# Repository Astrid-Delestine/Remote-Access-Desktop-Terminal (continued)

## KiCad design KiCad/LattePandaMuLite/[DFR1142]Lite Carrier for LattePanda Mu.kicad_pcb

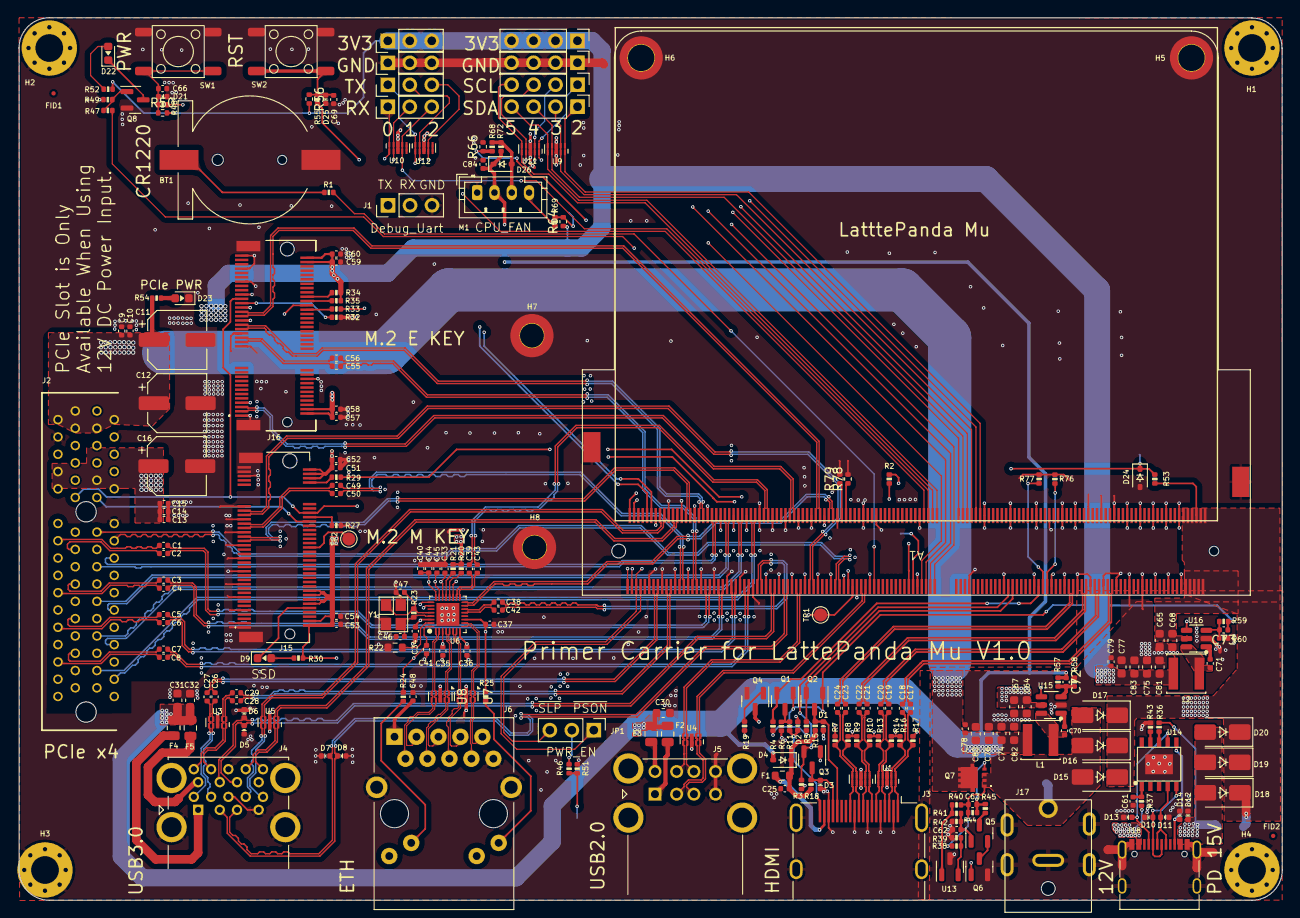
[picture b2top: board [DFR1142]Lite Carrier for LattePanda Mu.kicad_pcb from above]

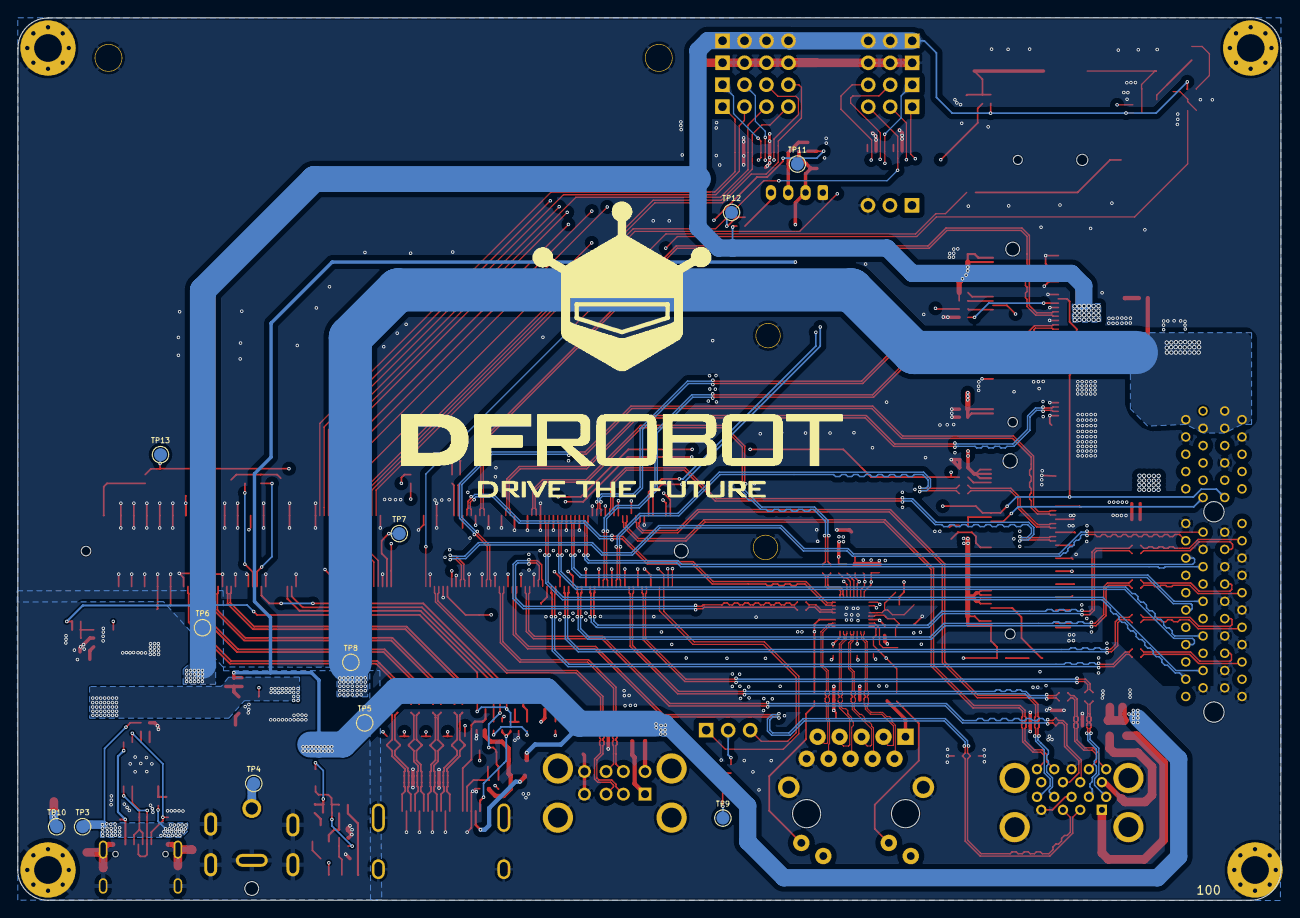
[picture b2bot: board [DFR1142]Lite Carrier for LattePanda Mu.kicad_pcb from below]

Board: 4 copper layers, 146.0 x 102.0 mm, 254 parts (11 on the bottom side), 204 nets.

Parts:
A1: LattePanda_Mu; LattePanda_Module_H8.0mm_Horizontal
BT1: Battery_Cell; Battery_Holder_CR1220_S8411-45R
C1, C2, C3, C4, C5, C6, C7, C8, C49, C50, C55, C56: 220nF/50V; C_0402_1005Metric
C9, C10, C13, C15, C17, C18, C19, C20, C21, C22, C23, C24, C25, C26, C27, C28, C29, C33, C34, C35, C36, C37, C38, C39, C40, C41, C42, C43, C45, C48, C52, C54, C58, C60, C70, C71, C78, C79, C84: 100nF/50V; C_0402_1005Metric
C11, C12: 100uF/25V; CP_Elec_6.3x7.7
C14, C44, C51, C53, C57, C59: 10uF/10V; C_0402_1005Metric
C16: 560uF/25V; CP_Elec_6.3x7.7
C30, C31, C32, C64, C65, C67, C68, C74, C75, C76, C77, C80, C81, C82, C83: 22uF/10V; C_0603_1608Metric
C46, C47, C72, C73: 12pF/50V; C_0402_1005Metric
C61, C62, C63, C66, C69: 1uF/16V; C_0402_1005Metric
D1, D2, D3, D5, D6, D7, D8, D10, D11, D21, D25: ESD5V0B03; D_0402_1005Metric
D4, D26: 1N5819WS; D_SOD-323
D9, D22, D23: LED_G; LED_0603_1608Metric
D12, D13, D14: PESD24VS1UL-N; D_0402_1005Metric
D15, D16, D17, D18, D19, D20: SS54; D_SMA
D24: 3V3 Izt=5mA; D_SOD-323
F1: 6V/50mA; R_0603_1608Metric
F2, F3: 6V/1A; Fuse_0805_2012Metric
F4: 6V/2A; R_0805_2012Metric
F5: 6V/2A; Fuse_0805_2012Metric
FID1, FID2: Fiducial; Fiducial_0.5mm_Mask1mm
H1, H2, H3, H4: MountingHole_Pad; MountingHole_3.2mm_M3_Pad_Via
H5, H6: MountingHole_Pad; MountingHole_3mm_M2_Pad_TopOnly
H7, H8: MountingHole_M2.0; MountingHole_2.7mm_M2_Pad_TopOnly
J1, J8, J10, J11, J14: Conn_01x03_Pin; PinHeader_1x03_P2.54mm_Vertical
J2: Bus_PCI_Express_x4; PCIe_x4_Gen3Slot_Connectors
J3: HDMI_A; HDMI_A_Molex_208658-1001_Horizontal
J4: USB3_A_Stacked; USB3_A_Molex_48406-0001_Horizontal_Stacked
J5: USB_A_Stacked; USB_A_CUI_UJ2-ADH-TH_Horizontal_Stacked
J6: RJ45_RB1-125B8G1A; RJ45_UDE_RB1-125B8G1A
J7, J9, J12, J13: Conn_01x04_Pin; PinHeader_1x04_P2.54mm_Vertical
J15: Bus_M.2_Socket_M; PCIe_M.2_Connectors_P=0.5mm_H=4.2mm_KeyM
J16: Bus_M.2_Socket_E; PCIe_M.2_Connectors_P=0.5mm_H=4.2mm_KeyE
J17: Barrel_Jack_Switch; DC_Jack_DC007B_30V_10A
J18: USB_C_Receptacle_USB2.0; USB_C_Receptacle_G-Switch_GT-USB-7010ASV
JP1: Jumper_3_Bridged12; PinHeader_1x03_P2.54mm_Vertical
L1, L2: 2.2uH/4.3A; L_Sunlord_SWPA4020S
M1: Fan_4pin; JST_PH_B4B-PH-K_1x04_P2.00mm_Vertical
Q1, Q5, Q6, Q8: 2N7002; SOT-23
Q2, Q3, Q4: 2SK3018; SOT-23
Q7: NCE30P28Q; MOSFET_PDFN8_3.3x3.3
R1, R11, R37, R47: 1K/1%; R_0402_1005Metric
R2, R20, R21, R34, R35, R36, R38, R40, R49, R50, R56, R58, R78, R79: 10K/1%; R_0402_1005Metric
R3, R5, R15, R18, R19, R30, R39, R52, R53: 2.2K/1%; R_0402_1005Metric
R4, R23: 1M/1%; R_0402_1005Metric
R6, R41, R42, R54, R59, R66, R68: 21.5K/1%; R_0402_1005Metric
R7, R8, R9, R10, R13, R14, R16, R17, R24, R25: 470R/1%; R_0402_1005Metric
R22: 2.49K/1%; R_0603_1608Metric
R27, R29, R32, R33: 0R/1%; R_0402_1005Metric
R43: 56K/1%; R_0402_1005Metric
R44, R45, R51, R76, R77: 100K/1%; R_0402_1005Metric
R46, R48, R55, R69: 100R/1%; R_0402_1005Metric
R57: 75K/1%; R_0402_1005Metric
R60, R64, R72: 4.7K/1%; R_0402_1005Metric
SW1, SW2: SW_Push; SW_Push_6x6x6
TP1, TP2, TP3, TP4, TP5, TP6, TP7, TP8, TP9, TP10, TP11, TP12, TP13: TestPoint; TestPoint_Pad_D1.5mm
U1, U2: TPAZ1023-04F; Diodes_UDFN-10_1.0x2.5mm_P0.5mm
U3, U4, U5, U7, U8, U9, U10, U11, U12: ULC0524P; Diodes_UDFN-10_1.0x2.5mm_P0.5mm
U6: RTL8111H-CG-RH; QFN-32-1EP_4x4mm_P0.4mm_EP2.65x2.65mm
U13: TL431DBZ; SOT-23
U14: CH224K; ESSOP-10-1EP_3.9x5mm_P1.0mm_EP3.2x2.3
U15, U16: SY8253ADC; TSOT-23-6
Y1: 25MHz; Crystal_SMD_3225-4Pin_3.2x2.5mm

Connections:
5V_HDMI_VCC: C25.1, D4.1 (K), F1.1, R15.1, R18.1
+1V0: C33.2, C34.2, C35.2, C36.2, C40.2, C44.2, U6.3 (AVDD10), U6.8 (AVDD10), U6.22 (DVDD10), U6.24 (REGOUT), U6.30 (AVDD10)
+3V3: C13.2, C14.2, C15.1, C16.1, C37.2, C41.2, C45.2, C51.2, C52.2, C53.2, C54.2, C57.2, C58.2, C59.2, C60.2, C73.1, C75.2, C77.2, C79.1, C81.2, C83.2, J2.A9 (+3.3V), J2.A10 (+3.3V), J2.B8 (+3.3V), J2.B10 (3.3Vaux), J13.1, J13.2, J13.3, J13.4, J14.1, J14.2, J14.3, J15.2 (3.3V), J15.4 (3.3V), J15.12 (3.3V), J15.14 (3.3V), J15.16 (3.3V), J15.18 (3.3V), J15.70 (3.3V), J15.72 (3.3V), J15.74 (3.3V), J16.2 (3.3V), J16.4 (3.3V), J16.72 (3.3V), J16.74 (3.3V), L2.2, Q1.1 (G), Q2.1 (G), Q3.1 (G), R3.1, R4.1, R5.1, R20.1, R21.1, R24.2, R25.2, R30.2, R34.2, R35.1, R50.2, R52.2, R56.2, R59.2, R64.1, TP6.1, U6.11 (AVDD33), U6.23 (VDDREG), U6.32 (AVDD33)
+5V: C30.2, C31.2, C32.2, C72.1, C74.2, C76.2, C78.1, C80.2, C82.2, C84.1, D4.2 (A), D26.1 (K), F2.1, F3.1, F4.1, F5.1, L1.2, M1.2 (+), R57.2, R72.1, TP5.1
+12V: C63.2, D15.2 (A), D16.2 (A), D17.2 (A), J17.1, Q7.1 (S_1), Q7.2 (S_2), Q7.3 (S_3), R38.2, R40.2, R44.2, TP4.1
+12VA: C9.1, C10.1, C11.1, C12.1, J2.A2 (+12V), J2.A3 (+12V), J2.B1 (+12V), J2.B2 (+12V), J2.B3 (+12V), Q7.5 (D_1), Q7.6 (D_2), Q7.7 (D_3), Q7.8 (D_4), Q7.9 (D_5), Q7.10 (D_6), Q7.11 (D_7), R54.1, TP8.1
+15V: D12.1 (K), D18.2 (A), D19.2 (A), D20.2 (A), J18.A4 (VBUS), J18.A9 (VBUS), J18.B4 (VBUS), J18.B9 (VBUS), R36.1, R37.1, TP3.1
+BATT: A1.115 (VBAT), R1.1
/Fan_Temp/FAN_1_PWM: A1.2 (FAN1_PWM), R64.2, R69.1, TP12.1
/Fan_Temp/FAN_1_TAC: A1.4 (FAN1_TAC), R66.1, R68.2, TP11.1
/GPIO/I2C2_SCL: A1.154 (I2C2_SCL), J9.1, U11.1, U11.10 (NC)
/GPIO/I2C2_SDA: A1.156 (I2C2_SDA), J7.1, U9.1, U9.10 (NC)
/GPIO/I2C3_SCL: A1.150 (I2C3_SCL), J9.2, U11.2, U11.9 (NC)
/GPIO/I2C3_SDA: A1.152 (I2C3_SDA), J7.2, U9.2, U9.9 (NC)
/GPIO/I2C4_SCL: A1.146 (I2C4_SCL), J9.3, U11.4, U11.7 (NC)
/GPIO/I2C4_SDA: A1.148 (I2C4_SDA), J7.3, U9.4, U9.7 (NC)
/GPIO/I2C5_SCL: A1.142 (I2C5_SCL), J9.4, U11.5, U11.6 (NC)
/GPIO/I2C5_SDA: A1.144 (I2C5_SDA), J7.4, U9.5, U9.6 (NC)
/GPIO/SOC_UART0_RX: A1.137 (UART0_RXD), J8.1, U10.1, U10.10 (NC)
/GPIO/SOC_UART0_TX: A1.139 (UART0_TXD), J10.1, U12.1, U12.10 (NC)
/GPIO/SOC_UART1_RX: A1.141 (UART1_RXD), J8.2, U10.2, U10.9 (NC)
/GPIO/SOC_UART1_TX: A1.143 (UART1_TXD), J10.2, U12.2, U12.9 (NC)
/GPIO/SOC_UART2_RX: A1.140 (UART2_RXD), J8.3, U10.4, U10.7 (NC)
/GPIO/SOC_UART2_TX: A1.138 (UART2_TXD), J10.3, U12.4, U12.7 (NC)
/Gigabit Ethernet/GbE_PCIe_CLK+: A1.94 (REFCLK4+), U6.15 (REFCLK_P)
/Gigabit Ethernet/GbE_PCIe_CLK-: A1.96 (REFCLK4-), U6.16 (REFCLK_N)
/Gigabit Ethernet/GbE_PCIe_RX+: A1.64 (HSIO6_RX+), C43.2
/Gigabit Ethernet/GbE_PCIe_RX-: A1.66 (HSIO6_RX-), C39.2
/Gigabit Ethernet/GbE_PCIe_TX+: A1.61 (HSIO6_TX+), C42.2
/Gigabit Ethernet/GbE_PCIe_TX-: A1.63 (HSIO6_TX-), C38.2
/Gigabit Ethernet/HSI+: C42.1, U6.13 (HSIP)
/Gigabit Ethernet/HSI-: C38.1, U6.14 (HSIN)
/Gigabit Ethernet/HSO+: C43.1, U6.17 (HSOP)
/Gigabit Ethernet/HSO-: C39.1, U6.18 (HSON)
/Gigabit Ethernet/LED1_1000: J6.L4, U6.26 (LED1)
/Gigabit Ethernet/LED2_ACT: J6.L2, U6.25 (LED2)
/Gigabit Ethernet/MDI0+: J6.R2 (TD1+), U6.1 (MDIP0), U8.5, U8.6 (NC)
/Gigabit Ethernet/MDI0-: J6.R3 (TD1-), U6.2 (MDIN0), U8.4, U8.7 (NC)
/Gigabit Ethernet/MDI1+: J6.R4 (TD2+), U6.4 (MDIP1), U8.2, U8.9 (NC)
/Gigabit Ethernet/MDI1-: J6.R5 (TD2-), U6.5 (MDIN1), U8.1, U8.10 (NC)
/Gigabit Ethernet/MDI2+: J6.R6 (TD3+), U6.6 (MDIP2), U7.5, U7.6 (NC)
/Gigabit Ethernet/MDI2-: J6.R7 (TD3-), U6.7 (MDIN2), U7.4, U7.7 (NC)
/Gigabit Ethernet/MDI3+: J6.R8 (TD4+), U6.9 (MDIP3), U7.2, U7.9 (NC)
/Gigabit Ethernet/MDI3-: J6.R9 (TD4-), U6.10 (MDIN3), U7.1, U7.10 (NC)
/HDMI/DDC_SCL: D1.2 (A2), J3.15 (SCL), Q2.3 (D), R15.2
/HDMI/DDC_SDA: D3.2 (A2), J3.16 (SDA), Q3.3 (D), R18.2
/HDMI/DDI_B_DDC_SCL: A1.171 (DDIB_DDC_SCL), Q2.2 (S), R5.2
/HDMI/DDI_B_DDC_SDA: A1.169 (DDIB_DDC_SDA), Q3.2 (S), R3.2
/HDMI/DDI_B_HPD: A1.183 (DDIB_HPD), Q1.2 (S), R4.2
/HDMI/DDI_B_TX0+: A1.217 (DDIB_TX0+), C17.1
/HDMI/DDI_B_TX0-: A1.215 (DDIB_TX0-), C18.1
/HDMI/DDI_B_TX1+: A1.211 (DDIB_TX1+), C19.1
/HDMI/DDI_B_TX1-: A1.209 (DDIB_TX1-), C20.1
/HDMI/DDI_B_TX2+: A1.205 (DDIB_TX2+), C21.1
/HDMI/DDI_B_TX2-: A1.203 (DDIB_TX2-), C22.1
/HDMI/DDI_B_TX3+: A1.199 (DDIB_TX3+), C23.1
/HDMI/DDI_B_TX3-: A1.197 (DDIB_TX3-), C24.1
/HDMI/HPD: D2.2 (A2), J3.19 (HPD), R11.2
/HDMI/TMDS_CK+: C23.2, J3.10 (CK+), R8.1, U2.4, U2.7 (NC)
/HDMI/TMDS_CK-: C24.2, J3.12 (CK-), R7.1, U2.5, U2.6 (NC)
/HDMI/TMDS_D0+: C21.2, J3.7 (D0+), R10.1, U2.1, U2.10 (NC)
/HDMI/TMDS_D0-: C22.2, J3.9 (D0-), R9.1, U2.2, U2.9 (NC)
/HDMI/TMDS_D1+: C19.2, J3.4 (D1+), R14.1, U1.4, U1.7 (NC)
/HDMI/TMDS_D1-: C20.2, J3.6 (D1-), R13.1, U1.5, U1.6 (NC)
/HDMI/TMDS_D2+: C17.2, J3.1 (D2+), R17.1, U1.1, U1.10 (NC)
/HDMI/TMDS_D2-: C18.2, J3.3 (D2-), R16.1, U1.2, U1.9 (NC)
/LattePanda Module/HSIO_0_TX+: A1.13 (HSIO0_TX+), C27.1
/LattePanda Module/HSIO_0_TX-: A1.15 (HSIO0_TX-), C26.1
/LattePanda Module/HSIO_1_TX+: A1.19 (HSIO1_TX+), C29.1
/LattePanda Module/HSIO_1_TX-: A1.21 (HSIO1_TX-), C28.1
/LattePanda Module/HSIO_2_RX+: A1.28 (HSIO2_RX+), J15.43 (PERp0/SATA-B-)
/LattePanda Module/HSIO_2_RX-: A1.30 (HSIO2_RX-), J15.41 (PERn0/SATA-B+)
/LattePanda Module/HSIO_2_TX+: A1.25 (HSIO2_TX+), C49.1
/LattePanda Module/HSIO_2_TX-: A1.27 (HSIO2_TX-), C50.1
/LattePanda Module/HSIO_3_RX+: A1.34 (HSIO3_RX+), J16.41 (PERp0)
/LattePanda Module/HSIO_3_RX-: A1.36 (HSIO3_RX-), J16.43 (PERn0)
/LattePanda Module/HSIO_3_TX+: A1.31 (HSIO3_TX+), C55.1
/LattePanda Module/HSIO_3_TX-: A1.33 (HSIO3_TX-), C56.1
/LattePanda Module/HSIO_8_RX+: A1.40 (HSIO8_RX+), J2.A16 (PERp0)
/LattePanda Module/HSIO_8_RX-: A1.42 (HSIO8_RX-), J2.A17 (PERn0)
/LattePanda Module/HSIO_8_TX+: A1.37 (HSIO8_TX+), C1.1
/LattePanda Module/HSIO_8_TX-: A1.39 (HSIO8_TX-), C2.1
/LattePanda Module/HSIO_9_RX+: A1.46 (HSIO9_RX+), J2.A21 (PERp1)
/LattePanda Module/HSIO_9_RX-: A1.48 (HSIO9_RX-), J2.A22 (PERn1)
/LattePanda Module/HSIO_9_TX+: A1.43 (HSIO9_TX+), C3.1
/LattePanda Module/HSIO_9_TX-: A1.45 (HSIO9_TX-), C4.1
/LattePanda Module/HSIO_10_RX+: A1.52 (HSIO10_RX+), J2.A25 (PERp2)
/LattePanda Module/HSIO_10_RX-: A1.54 (HSIO10_RX-), J2.A26 (PERn2)
/LattePanda Module/HSIO_10_TX+: A1.49 (HSIO10_TX+), C5.1
/LattePanda Module/HSIO_10_TX-: A1.51 (HSIO10_TX-), C6.1
/LattePanda Module/HSIO_11_RX+: A1.58 (HSIO11_RX+), J2.A29 (PERp3)
/LattePanda Module/HSIO_11_RX-: A1.60 (HSIO11_RX-), J2.A30 (PERn3)
/LattePanda Module/HSIO_11_TX+: A1.55 (HSIO11_TX+), C7.1
/LattePanda Module/HSIO_11_TX-: A1.57 (HSIO11_TX-), C8.1
/LattePanda Module/REFCLK0+: A1.85 (REFCLK0+), J15.53 (REFCLKn)
/LattePanda Module/REFCLK0-: A1.87 (REFCLK0-), J15.55 (REFCLKp)
/LattePanda Module/REFCLK2+: A1.97 (REFCLK2+), J2.A13 (REFCLK+)
/LattePanda Module/REFCLK2-: A1.99 (REFCLK2-), J2.A14 (REFCLK-)
/LattePanda Module/REFCLK3+: A1.88 (REFCLK3+), J16.47 (REFCLKp0)
/LattePanda Module/REFCLK3-: A1.90 (REFCLK3-), J16.49 (REFCLKn0)
/LattePanda Module/SLS_S3: A1.7 (SLS_S3), JP1.3 (B)
/LattePanda Module/SUSCLK_WIFI: A1.131 (SUSCLK), R29.2, R33.2
/LattePanda Module/USB_2_P7+: A1.76 (USB2_P7+), J16.3 (USB_D+)
/LattePanda Module/USB_2_P7-: A1.78 (USB2_P7-), J16.5 (USB_D-)
/LattePanda Module/~PWR_SW: A1.1 (~PWRBTN), R48.2
/LattePanda Module/~RST_SW: A1.3 (~RSTBTN), R55.2
/M.2 E&M Key/CON_PCIE_TX_0+: C55.2, J16.35 (PETp0)
/M.2 E&M Key/CON_PCIE_TX_0-: C56.2, J16.37 (PETn0)
/M.2 E&M Key/CON_PCIE_TX_1+: C49.2, J15.49 (PETp0/SATA-A+)
/M.2 E&M Key/CON_PCIE_TX_1-: C50.2, J15.47 (PETn0/SATA-A-)
/M.2 E&M Key/~CLKREQE: J16.53 (~CLKREQ3), R32.1
/M.2 E&M Key/~CLKREQM: J15.52 (~CLKREQ), R27.1
/PCIe x4/PCIE30_TX0_N: C2.2, J2.B15 (PETn0)
/PCIe x4/PCIE30_TX0_P: C1.2, J2.B14 (PETp0)
/PCIe x4/PCIE30_TX1_N: C4.2, J2.B20 (PETn1)
/PCIe x4/PCIE30_TX1_P: C3.2, J2.B19 (PETp1)
/PCIe x4/PCIE30_TX2_N: C6.2, J2.B24 (PETn2)
/PCIe x4/PCIE30_TX2_P: C5.2, J2.B23 (PETp2)
/PCIe x4/PCIE30_TX3_N: C8.2, J2.B28 (PETn3)
/PCIe x4/PCIE30_TX3_P: C7.2, J2.B27 (PETp3)
/PSU/CC1: D13.1 (K), J18.A5 (CC1), U14.7 (CC1)
/PSU/CC2: D14.1 (K), J18.B5 (CC2), U14.6 (CC2)
/PSU/PWR_C_D+: D11.2 (A2), J18.A6 (D+), J18.B6 (D+), U14.4 (DP)
/PSU/PWR_C_D-: D10.2 (A2), J18.A7 (D-), J18.B7 (D-), U14.5 (DM)
/PSU/PWR_EN: Q6.1 (G), R46.2, R51.2, TP9.1, U15.4 (EN), U16.4 (EN)
/USB2.0&USB3.0/CON_USB1_D_N: A1.109 (USB2_P5-), J5.2 (D1-), U4.2, U4.9 (NC)
/USB2.0&USB3.0/CON_USB1_D_P: A1.111 (USB2_P5+), J5.3 (D1+), U4.1, U4.10 (NC)
/USB2.0&USB3.0/CON_USB2_D_N: A1.79 (USB2_P3-), J5.6 (D2-), U4.5, U4.6 (NC)
/USB2.0&USB3.0/CON_USB2_D_P: A1.81 (USB2_P3+), J5.7 (D2+), U4.4, U4.7 (NC)
/USB2.0&USB3.0/CON_USB3_D_N: A1.73 (USB2_P2-), D8.2 (A2), J4.2 (D1-)
/USB2.0&USB3.0/CON_USB3_D_P: A1.75 (USB2_P2+), D7.2 (A2), J4.3 (D1+)
/USB2.0&USB3.0/CON_USB3_SSRX_N: A1.18 (HSIO0_RX-), J4.5 (SSRX1-), U5.4, U5.7 (NC)
/USB2.0&USB3.0/CON_USB3_SSRX_P: A1.16 (HSIO0_RX+), J4.6 (SSRX1+), U5.5, U5.6 (NC)
/USB2.0&USB3.0/CON_USB3_SSTX_N: C26.2, J4.8 (SSTX1-), U3.4, U3.7 (NC)
/USB2.0&USB3.0/CON_USB3_SSTX_P: C27.2, J4.9 (SSTX1+), U3.5, U3.6 (NC)
/USB2.0&USB3.0/CON_USB4_D_N: A1.67 (USB2_P1-), D6.2 (A2), J4.11 (D2-)
/USB2.0&USB3.0/CON_USB4_D_P: A1.69 (USB2_P1+), D5.2 (A2), J4.12 (D2+)
/USB2.0&USB3.0/CON_USB4_SSRX_N: A1.24 (HSIO1_RX-), J4.14 (SSRX2-), U5.1, U5.10 (NC)
/USB2.0&USB3.0/CON_USB4_SSRX_P: A1.22 (HSIO1_RX+), J4.15 (SSRX2+), U5.2, U5.9 (NC)
/USB2.0&USB3.0/CON_USB4_SSTX_N: C28.2, J4.17 (SSTX2-), U3.1, U3.10 (NC)
/USB2.0&USB3.0/CON_USB4_SSTX_P: C29.2, J4.18 (SSTX2+), U3.2, U3.9 (NC)
/~PLT_RST: A1.105 (~PLTRST), J2.A11 (~PERST), J15.50 (~PERST), J16.52 (~PERST0), TP1.1, U6.19 (PERSTB)
/~PWR_LED/~PSON: A1.5 (SLS_S0), JP1.1 (A), R19.1, R47.1
/~WAKE: A1.103 (~WAKE), J2.B11 (~WAKE), J15.54 (~PEWAKE), J16.55 (~PEWAKE0)
GND: A1.11 (GND), A1.14 (GND), A1.17 (GND), A1.20 (GND), A1.23 (GND), A1.26 (GND), A1.29 (GND), A1.32 (GND), A1.35 (GND), A1.38 (GND), A1.41 (GND), A1.44 (GND), A1.47 (GND), A1.50 (GND), A1.53 (GND), A1.56 (GND), A1.59 (GND), A1.62 (GND), A1.65 (GND), A1.68 (GND), A1.71 (GND), A1.74 (GND), A1.77 (GND), A1.80 (GND), A1.83 (GND), A1.86 (GND), A1.89 (GND), A1.92 (GND), A1.95 (GND), A1.98 (GND), A1.101 (GND), A1.107 (GND), A1.110 (GND), A1.113 (GND), A1.116 (GND), A1.135 (GND), A1.136 (GND), A1.151 (GND), A1.158 (GND), A1.167 (GND), A1.170 (GND), A1.181 (GND), A1.182 (GND), A1.188 (GND), A1.189 (GND), A1.194 (GND), A1.195 (GND), A1.200 (GND), A1.201 (GND), A1.206 (GND), A1.207 (GND), A1.212 (GND), A1.213 (GND), A1.218 (GND), A1.219 (GND), A1.224 (GND), A1.225 (GND), A1.230 (GND), A1.231 (GND), A1.236 (GND), A1.237 (GND), A1.242 (GND), A1.243 (GND), A1.248 (GND), A1.249 (GND), A1.MP (Mountinge_Pads), BT1.2 (-), C9.2, C10.2, C11.2, C12.2, C13.1, C14.1, C15.2, C16.2, C25.2, C30.1, C31.1, C32.1, C33.1, C34.1, C35.1, C36.1, C37.1, C40.1, C41.1, C44.1, C45.1, C46.1, C47.1, C48.2, C51.1, C52.1, C53.1, C54.1, C57.1, C58.1, C59.1, C60.1, C61.2, C62.2, C64.1, C65.1, C66.2, C67.1, C68.1, C69.2, C74.1, C75.1, C76.1, C77.1, C78.2, C79.2, C80.1, C81.1, C82.1, C83.1, C84.2, D1.1 (A1), D2.1 (A1), D3.1 (A1), D5.1 (A1), D6.1 (A1), D7.1 (A1), D8.1 (A1), D10.1 (A1), D11.1 (A1), D12.2 (A), D13.2 (A), D14.2 (A), D21.1 (A1), D23.1 (K), D24.2 (A), D25.1 (A1), H1.1, H2.1, H3.1, H4.1, H5.1, H6.1, H7.1, H8.1, J1.3, J2.A1 (~PRSNT1), J2.A4 (GND), J2.A12 (GND), J2.A15 (GND), J2.A18 (GND), J2.A20 (GND), J2.A23 (GND), J2.A24 (GND), J2.A27 (GND), J2.A28 (GND), J2.A31 (GND), J2.B4 (GND), J2.B7 (GND), J2.B13 (GND), J2.B16 (GND), J2.B17 (~PRSNT2), J2.B18 (GND), J2.B21 (GND), J2.B22 (GND), J2.B25 (GND), J2.B26 (GND), J2.B29 (GND), J2.B31 (~PRSNT2), J2.B32 (GND), J3.2 (D2S), J3.5 (D1S), J3.8 (D0S), J3.11 (CKS), J3.17 (GND), J3.SH, J4.4 (GND1), J4.7 (DRAIN1), J4.13 (GND2), J4.16 (DRAIN2), J4.19 (SHIELD), J5.4 (GND1), J5.8 (GND2), J5.9 (Shield), J6.R10 (GND), J6.SH, J11.1, J11.2, J11.3, J12.1, J12.2, J12.3, J12.4, J15.1 (GND), J15.3 (GND), J15.9 (GND), J15.15 (GND), J15.21 (GND), J15.27 (GND), J15.33 (GND), J15.39 (GND), J15.45 (GND), J15.51 (GND), J15.57 (GND), J15.71 (GND), J15.73 (GND), J15.75 (GND), J15.MP1, J15.MP2, J16.1 (GND), J16.7 (GND), J16.18 (GND), J16.33 (GND), J16.39 (GND), J16.45 (GND), J16.51 (GND), J16.57 (GND), J16.63 (GND), J16.69 (GND), J16.75 (GND), J16.MP1, J16.MP2, J17.2, J17.3, J18.A1 (GND), J18.A12 (GND), J18.B1 (GND), J18.B12 (GND), J18.S1 (SHIELD), M1.1 (-), Q4.2 (S), Q6.2 (S), Q8.2 (S), R6.2, R22.1, R27.2, R32.2, R39.1, R42.1, R43.2, R49.1, R51.1, R58.1, R60.1, R66.2, R76.2, R77.2, R78.2, R79.2, SW1.2, SW2.2, U1.3 (VSS), U1.8 (VSS), U2.3 (VSS), U2.8 (VSS), U3.3 (VSS), U3.8 (VSS), U4.3 (VSS), U4.8 (VSS), U5.3 (VSS), U5.8 (VSS), U6.33 (GND), U7.3 (VSS), U7.8 (VSS), U8.3 (VSS), U8.8 (VSS), U9.3 (VSS), U9.8 (VSS), U10.3 (VSS), U10.8 (VSS), U11.3 (VSS), U11.8 (VSS), U12.3 (VSS), U12.8 (VSS), U13.3 (A), U14.0 (GND), U15.2 (GND), U16.2 (GND), Y1.2, Y1.4
unnamed: A1.12 (SIO_UART_RX), J1.2
unnamed: A1.10 (SIO_UART_TX), J1.1
unnamed: A1.187 (TCP0_HPD), R76.1
unnamed: A1.185 (TCP1_HPD), R77.1
unnamed: A1.133 (~BIOS_SEL), R2.1, TP7.1
unnamed: A1.100 (~CLKREQ3), R79.1
unnamed: A1.102 (~CLKREQ4), R78.1
unnamed: BT1.1 (+), R1.2
unnamed: D9.2 (A), R30.1
unnamed: D9.1 (K), J15.10 (DAS/~DSS/~LED1)
unnamed: C66.1, D21.2 (A2), R48.1, R50.1, SW1.1
unnamed: D22.2 (A), R52.1
unnamed: D22.1 (K), Q8.3 (D)
unnamed: D23.2 (A), R54.2
unnamed: C69.1, D25.2 (A2), R55.1, R56.1, SW2.1
unnamed: D26.2 (A), M1.3 (Tacho), R68.1, R72.2
unnamed: F1.2, J3.18 (+5V)
unnamed: F4.2, J4.1 (VBUS1)
unnamed: F5.2, J4.10 (VBUS2)
unnamed: F2.2, J5.1 (VBUS1)
unnamed: F3.2, J5.5 (VBUS2)
unnamed: C48.1, J6.R1 (CT)
unnamed: J6.L1, R25.1
unnamed: J6.L3, R24.1
unnamed: J15.38 (DEVSLP), TP2.1
unnamed: J15.68 (SUSCLK), R29.1
unnamed: J16.50 (SUSCLK), R33.1
unnamed: J16.56 (~W_DISABLE1), R34.1
unnamed: J16.54 (~W_DISABLE2), R35.2
unnamed: JP1.2 (C), R46.1
unnamed: M1.4 (PWM), R69.2
unnamed: Q1.3 (D), R6.1, R11.1
unnamed: Q4.3 (D), R7.2, R8.2, R9.2, R10.2, R13.2, R14.2, R16.2, R17.2
unnamed: Q4.1 (G), R19.2
unnamed: Q5.3 (D), R45.1
unnamed: C62.1, Q5.1 (G), R41.1, R42.2
unnamed: Q5.2 (S), Q6.3 (D)
unnamed: C63.1, Q7.4 (G), R44.1, R45.2
unnamed: Q8.1 (G), R47.2, R49.2
unnamed: C47.2, R23.2, U6.28 (CKXTAL1), Y1.1
unnamed: C46.2, R23.1, U6.29 (CKXTAL2), Y1.3
unnamed: R20.2, U6.20 (ISOLATEB)
unnamed: R21.2, U6.21 (LANWAKEB)
unnamed: R22.2, U6.31 (RSET)
unnamed: U10.5, U10.6 (NC)
unnamed: U12.5, U12.6 (NC)
unnamed: R40.1, R41.2, U13.1 (K)
unnamed: R38.1, R39.2, U13.2 (REF)
unnamed: R43.1, U14.9 (CFG1)
unnamed: R36.2, U14.8 (VBUS)
unnamed: C61.1, R37.2, U14.1 (VDD)
unnamed: C70.2, U15.1 (BOOST)
unnamed: C72.2, R57.1, R58.2, U15.3 (FB)
unnamed: C70.1, L1.1, U15.6 (SW)
unnamed: C71.2, U16.1 (BOOST)
unnamed: C73.2, R59.1, R60.2, U16.3 (FB)
unnamed: C71.1, L2.1, U16.6 (SW)
VDC: A1.250 (VIN), A1.251 (VIN), A1.252 (VIN), A1.253 (VIN), A1.254 (VIN), A1.255 (VIN), A1.256 (VIN), A1.257 (VIN), A1.258 (VIN), A1.259 (VIN), A1.260 (VIN), C64.2, C65.2, C67.2, C68.2, D15.1 (K), D16.1 (K), D17.1 (K), D18.1 (K), D19.1 (K), D20.1 (K), R53.1, TP10.1, U15.5 (VIN), U16.5 (VIN)
VPullup: D24.1 (K), R2.2, R53.2, TP13.1

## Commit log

2024-12-18 Create Kicad Files
2025-01-10 setup for more in depth work
2025-01-10 Added Notes
2025-01-12 Add logs and update keyboard
2025-01-12 Update gitignore to not include invoices
2025-01-17 Update note2.md
    added more keyboard options to try
2025-01-21 Weekend work updates
2025-01-22 Create anntenna.md
    Added antenna areas of doc
2025-02-04 Create note3.md
    added note 3 regarding BMS stuff
2025-02-05 Add data from KiCAD and review
2025-02-07 kiCad BMS sadness
2025-02-08 finalized midterm review
2025-02-08 added list of goals for next 5 wks
2025-02-08 modified the table on bms info
2025-02-10 BMS circuitry
2025-02-12 Added kicad USBC controller and connected VBUS
2025-02-12 tb4 prooved to be too diffucult/expensive...
    Issue: would cost $200+ to devlop for this chipset
2025-02-12 added file note4.md
2025-02-13 updated time log
2025-02-17 Update BMS
2025-02-17 Added new files
2025-02-20 Add new notes; update component references in schematics and footprints, and complete charging design
2025-02-24 VRM update?
2025-02-24 remove VRM b.c naming broke
2025-02-24 add back VRM
2025-02-24 added volage stuffs
2025-02-25 Update VRM stuff
2025-02-26 Added example and updated power path
2025-02-26 Modified Power Stages
2025-02-26 Connected m.2 E Key
2025-02-27 Added HDMI connection and marked section for review in schematics; updated column widths in PRL file; added new operating values CSV files for power calculations.
2025-02-27 Started process of BMS review
2025-02-28 2x checked all schematics
2025-02-28 Pre-Annotate FULL, add usb
2025-03-02 Added Libs and DOCS
2025-03-02 Added Generated BOM
2025-03-02 Update BOM
2025-03-03 Sourced and documented all parts
2025-03-03 Push before Board Layout
2025-03-03 placed board components, with errors
2025-03-03 Removed Old BOM data
2025-03-03 Update Merged_BOM_Data
    part #s added
2025-03-03 Updated Layout
2025-03-04 Placed a lot of components
2025-03-05 added Trace width table
2025-03-06 End Of day commit
2025-03-06 Most of the way thru routing
2025-03-07 Wrong footprint for keyswitches, creating save point
2025-03-07 push prior to autorouting
2025-03-08 Adequitely Passing DRC
2025-03-08 finalized board layout
2025-03-10 2x checing of bom on JLCPCB
2025-03-11 Generate Gerbers and Order PCB
2025-06-27 Added the License that I should have a while ago
2025-07-17 Created and finalized alpha branch
2025-07-17 Remove obsolete files and update README for project status
    - Deleted the RDAT_BOM_NEW_NEW.ods file as it is no longer needed.
    - Updated README.md to reflect the project's transition from coursework to personal project, added notes on versioning, and removed outdated information.
    - Removed the time logging script (time_clock.zsh) and its associated log file (time_log.csv) as they are no longer in use.
